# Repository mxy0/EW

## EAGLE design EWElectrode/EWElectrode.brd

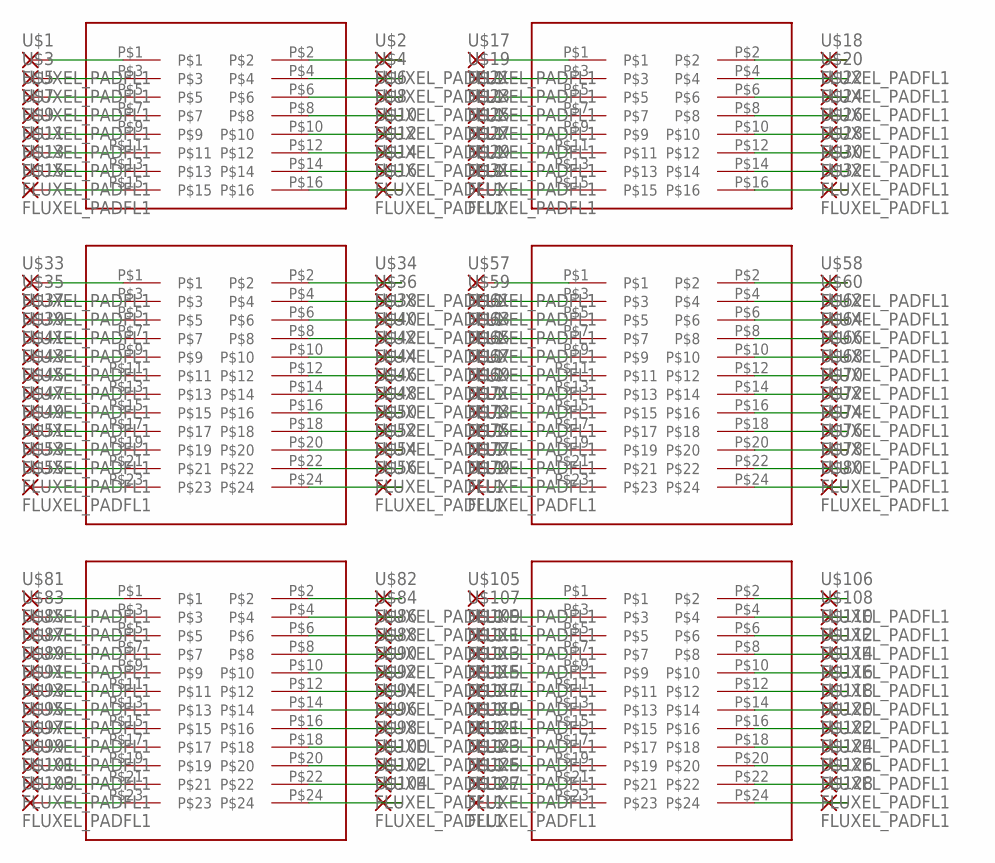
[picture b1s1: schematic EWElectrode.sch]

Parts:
J1, J2: M20-876P_8X2
J3, J4, J5, J6: M20-876P_12X2
U$1, U$2, U$3, U$4, U$5, U$6, U$7, U$8, U$9, U$10, U$11, U$12, U$13, U$14, U$15, U$16, U$17, U$18, U$19, U$20, U$21, U$22, U$23, U$24, U$25, U$26, U$27, U$28, U$29, U$30, U$31, U$32, U$33, U$34, U$35, U$36, U$37, U$38, U$39, U$40, U$41, U$42, U$43, U$44, U$45, U$46, U$47, U$48, U$49, U$50, U$51, U$52, U$53, U$54, U$55, U$56, U$57, U$58, U$59, U$60, U$61, U$62, U$63, U$64, U$65, U$66, U$67, U$68, U$69, U$70, U$71, U$72, U$73, U$74, U$75, U$76, U$77, U$78, U$79, U$80, U$81, U$82, U$83, U$84, U$85, U$86, U$87, U$88, U$89, U$90, U$91, U$92, U$93, U$94, U$95, U$96, U$97, U$98, U$99, U$100, U$101, U$102, U$103, U$104, U$105, U$106, U$107, U$108, U$109, U$110, U$111, U$112, U$113, U$114, U$115, U$116, U$117, U$118, U$119, U$120, U$121, U$122, U$123, U$124, U$125, U$126, U$127, U$128: FLUXEL_PADFL1; FLUXEL_PAD

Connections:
EW1: J1.P$1, U$1.1
EW2: J1.P$3, U$3.1
EW3: J1.P$5, U$5.1
EW4: J1.P$7, U$7.1
EW5: J1.P$9, U$9.1
EW6: J1.P$11, U$11.1
EW7: J1.P$13, U$13.1
EW8: J1.P$15, U$15.1
EW9: J1.P$2, U$2.1
EW10: J1.P$4, U$4.1
EW11: J1.P$6, U$6.1
EW12: J1.P$8, U$8.1
EW13: J1.P$10, U$10.1
EW14: J1.P$12, U$12.1
EW15: J1.P$14, U$14.1
EW16: J1.P$16, U$16.1
EW17: J2.P$1, U$17.1
EW18: J2.P$3, U$19.1
EW19: J2.P$5, U$21.1
EW20: J2.P$7, U$23.1
EW21: J2.P$9, U$25.1
EW22: J2.P$11, U$27.1
EW23: J2.P$13, U$29.1
EW24: J2.P$15, U$31.1
EW25: J2.P$2, U$18.1
EW26: J2.P$4, U$20.1
EW27: J2.P$6, U$22.1
EW28: J2.P$8, U$24.1
EW29: J2.P$10, U$26.1
EW30: J2.P$12, U$28.1
EW31: J2.P$14, U$30.1
EW32: J2.P$16, U$32.1
EW34: J3.P$3, U$35.1
EW35: J3.P$5, U$37.1
EW36: J3.P$7, U$39.1
EW37: J3.P$9, U$41.1
EW38: J3.P$11, U$43.1
EW39: J3.P$13, U$45.1
EW40: J3.P$15, U$47.1
EW41: J3.P$17, U$49.1
EW42: J3.P$19, U$51.1
EW44: J3.P$23, U$55.1
EW45: J3.P$2, U$34.1
EW46: J3.P$4, U$36.1
EW47: J3.P$6, U$38.1
EW48: J3.P$8, U$40.1
EW49: J3.P$10, U$42.1
EW50: J3.P$12, U$44.1
EW51: J3.P$14, U$46.1
EW52: J3.P$16, U$48.1
EW53: J3.P$18, U$50.1
EW54: J3.P$20, U$52.1
EW55: J3.P$22, U$54.1
EW56: J3.P$24, U$56.1
EW57: J4.P$1, U$57.1
EW58: J4.P$3, U$59.1
EW59: J4.P$5, U$61.1
EW60: J4.P$7, U$63.1
EW61: J4.P$9, U$65.1
EW62: J4.P$11, U$67.1
EW63: J4.P$13, U$69.1
EW64: J4.P$15, U$71.1
EW65: J4.P$17, U$73.1
EW66: J4.P$19, U$75.1
EW67: J4.P$21, U$77.1
EW68: J4.P$23, U$79.1
EW69: J4.P$2, U$58.1
EW70: J4.P$4, U$60.1
EW71: J4.P$6, U$62.1
EW72: J4.P$8, U$64.1
EW73: J4.P$10, U$66.1
EW74: J4.P$12, U$68.1
EW75: J4.P$14, U$70.1
EW76: J4.P$16, U$72.1
EW77: J4.P$18, U$74.1
EW78: J4.P$20, U$76.1
EW79: J4.P$22, U$78.1
EW80: J4.P$24, U$80.1
EW81: J5.P$1, U$81.1
EW82: J5.P$3, U$83.1
EW83: J5.P$5, U$85.1
EW84: J5.P$7, U$87.1
EW85: J5.P$9, U$89.1
EW86: J5.P$11, U$91.1
EW87: J5.P$13, U$93.1
EW88: J5.P$15, U$95.1
EW90: J5.P$19, U$99.1
EW91: J5.P$21, U$101.1
EW92: J5.P$23, U$103.1
EW93: J5.P$2, U$82.1
EW94: J5.P$4, U$84.1
EW95: J5.P$6, U$86.1
EW96: J5.P$8, U$88.1
EW97: J5.P$10, U$90.1
EW98: J5.P$12, U$92.1
EW99: J5.P$14, U$94.1
EW100: J5.P$16, U$96.1
EW102: J5.P$20, U$100.1
EW105: J6.P$1, U$105.1
EW106: J6.P$3, U$107.1
EW107: J6.P$5, U$109.1
EW108: J6.P$7, U$111.1
EW109: J6.P$9, U$113.1
EW110: J6.P$11, U$115.1
EW111: J6.P$13, U$117.1
EW112: J6.P$15, U$119.1
EW113: J6.P$17, U$121.1
EW114: J6.P$19, U$123.1
EW115: J6.P$21, U$125.1
EW116: J6.P$23, U$127.1
EW117: J6.P$2, U$106.1
EW118: J6.P$4, U$108.1
EW119: J6.P$6, U$110.1
EW120: J6.P$8, U$112.1
EW121: J6.P$10, U$114.1
EW122: J6.P$12, U$116.1
EW123: J6.P$14, U$118.1
EW124: J6.P$16, U$120.1
EW125: J6.P$18, U$122.1
EW126: J6.P$20, U$124.1
EW127: J6.P$22, U$126.1
EW128: J6.P$24, U$128.1
EW137: J3.P$21, U$53.1
EW166: J5.P$18, U$98.1
EW236: J5.P$17, U$97.1
EW261: J3.P$1, U$33.1
EW287: J5.P$22, U$102.1
EW289: J5.P$24, U$104.1

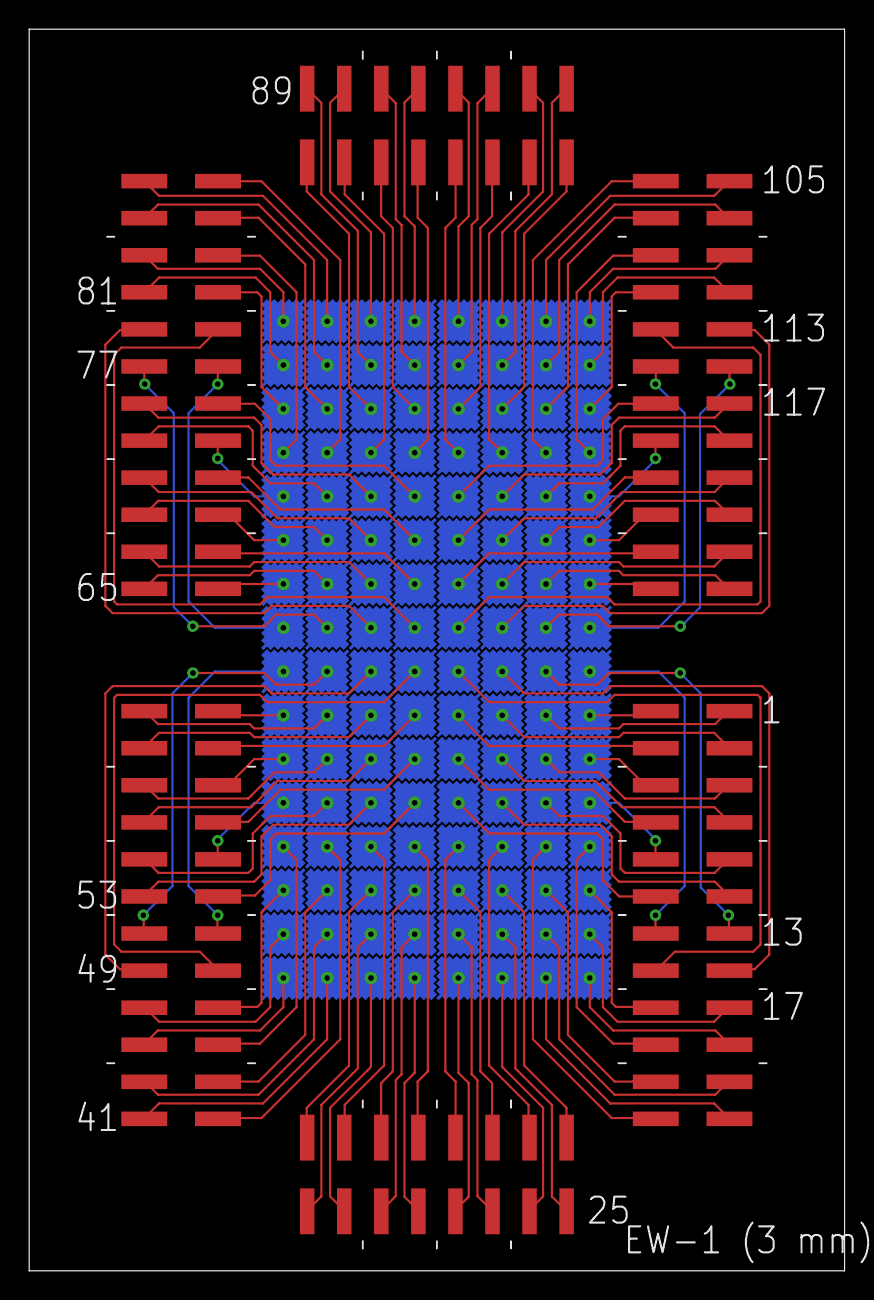
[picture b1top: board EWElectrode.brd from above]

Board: 2 copper layers, 55.9 x 85.1 mm, 134 parts (0 on the bottom side), 128 nets.

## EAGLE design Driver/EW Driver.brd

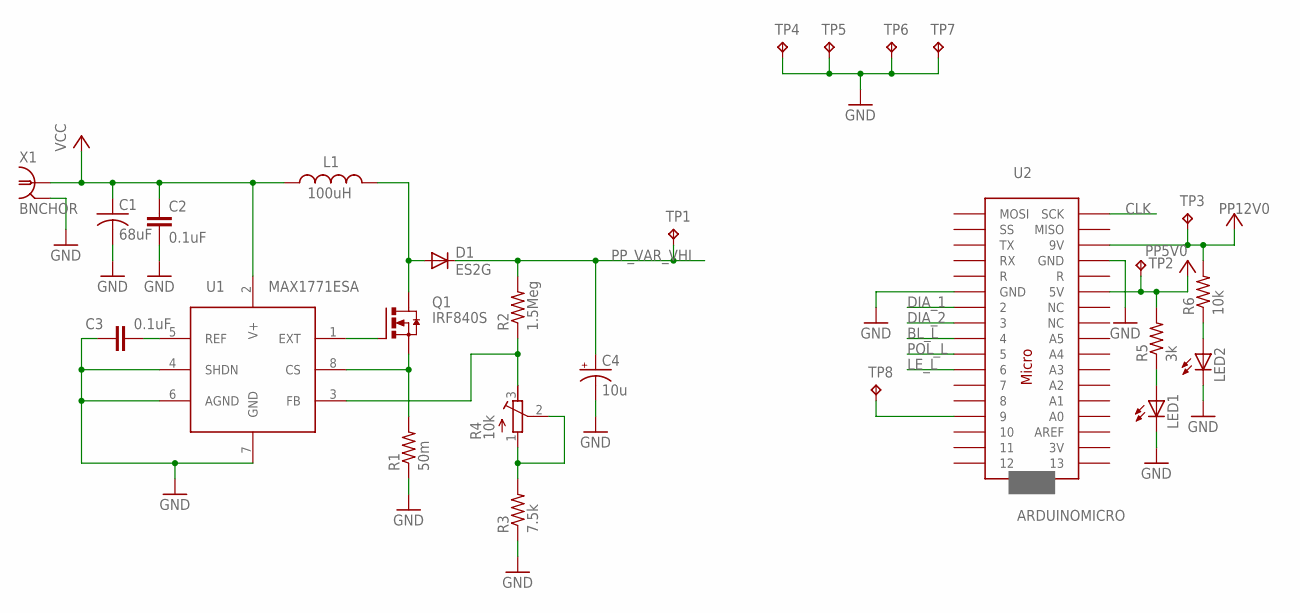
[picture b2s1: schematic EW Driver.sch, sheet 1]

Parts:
C1: 68uF; C2312
C2, C3: 0.1uF; C1206
C4: 10u; PANASONIC_D
D1: ES2G; DO214AA
L1: 100uH; P0762NL
LED1, LED2: LED_ESML0603; LED_SML0603
Q1: IRF840S; D2PACK
R1: 50m; R1206
R2: 1.5Meg; R1206
R3: 7.5k; R0805
R4: 10k; RTRIM3296P
R5: 3k; R0805
R6: 10k; R0805
TP1, TP2, TP3, TP8: TP; TEST_SMT
TP4, TP5, TP6, TP7: TP063; TEST_TH
U1: MAX1771ESA; SO08
U2: ARDUINOMICRO
X1: BNCHOR; BNC_HOR

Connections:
BL_L: U2.P$9 (4); also elsewhere on the board
CLK: U2.P$18 (SCK); also elsewhere on the board
DIA_1: U2.P$11 (2); also elsewhere on the board
DIA_2: U2.P$10 (3); also elsewhere on the board
GND: C1.2, C2.2, C3.2, C4.-, LED1.C, LED2.C, R1.1, R3.1, TP4.TP, TP5.TP, TP6.TP, TP7.TP, U1.4 (SHDN), U1.6 (AGND), U1.7 (GND), U2.P$12 (GND), U2.P$21 (GND), X1.2, X1.3 (2); also elsewhere on the board
LE_L: U2.P$7 (6); also elsewhere on the board
unnamed: C3.1, U1.5 (REF)
unnamed: Q1.1 (G), U1.1 (EXT)
unnamed: Q1.3 (S), R1.2, U1.8 (CS)
unnamed: D1.A, L1.2, Q1.2 (D)
unnamed: R3.2, R4.1 (A), R4.2 (S)
unnamed: R2.1, R4.3 (E), U1.3 (FB)
unnamed: LED1.A, R5.1
unnamed: LED2.A, R6.1
unnamed: TP8.TP, U2.P$4 (9)
POL_L: U2.P$8 (5); also elsewhere on the board
PP5V0: R5.2, TP2.TP, U2.P$23 (5V); also elsewhere on the board
PP12V0: C1.1, C2.1, L1.1, R6.2, TP3.TP, U1.2 (V+), U2.P$20 (9V), X1.1
PP_VAR_VHI: C4.+, D1.C, R2.2, TP1.TP; also elsewhere on the board

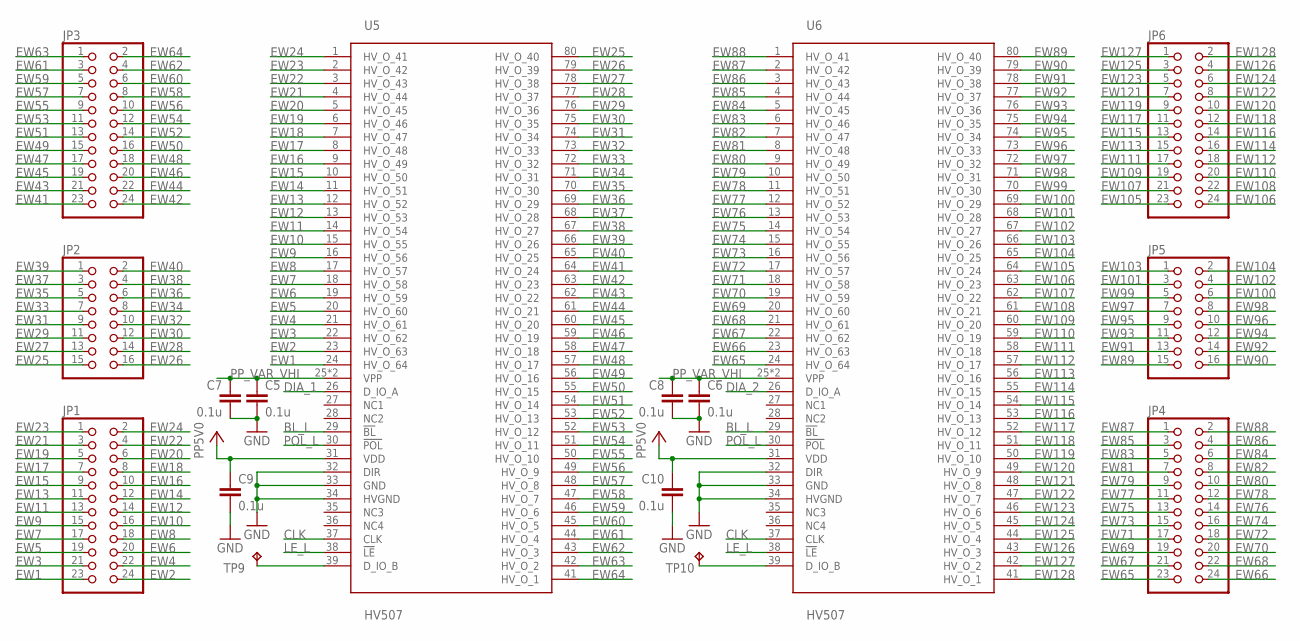
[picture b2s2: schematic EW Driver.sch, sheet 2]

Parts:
C5, C6, C7, C8, C9, C10: 0.1u; C1206
JP1, JP3, JP4, JP6: PINHD-2X12_0.05; 2X12_0.05
JP2, JP5: PINHD-2X8_0.05; 2X8_0.05
TP9, TP10: TP; TEST_SMT
U5, U6: HV507; HV507PG-G

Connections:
BL_L: U5.29 (!BL), U6.29 (!BL); also elsewhere on the board
CLK: U5.37 (CLK), U6.37 (CLK); also elsewhere on the board
DIA_1: U5.26 (D_IO_A); also elsewhere on the board
DIA_2: U6.26 (D_IO_A); also elsewhere on the board
EW1: JP1.23, U5.24 (HV_O_64)
EW2: JP1.24, U5.23 (HV_O_63)
EW3: JP1.21, U5.22 (HV_O_62)
EW4: JP1.22, U5.21 (HV_O_61)
EW5: JP1.19, U5.20 (HV_O_60)
EW6: JP1.20, U5.19 (HV_O_59)
EW7: JP1.17, U5.18 (HV_O_58)
EW8: JP1.18, U5.17 (HV_O_57)
EW9: JP1.15, U5.16 (HV_O_56)
EW10: JP1.16, U5.15 (HV_O_55)
EW11: JP1.13, U5.14 (HV_O_54)
EW12: JP1.14, U5.13 (HV_O_53)
EW13: JP1.11, U5.12 (HV_O_52)
EW14: JP1.12, U5.11 (HV_O_51)
EW15: JP1.9, U5.10 (HV_O_50)
EW16: JP1.10, U5.9 (HV_O_49)
EW17: JP1.7, U5.8 (HV_O_48)
EW18: JP1.8, U5.7 (HV_O_47)
EW19: JP1.5, U5.6 (HV_O_46)
EW20: JP1.6, U5.5 (HV_O_45)
EW21: JP1.3, U5.4 (HV_O_44)
EW22: JP1.4, U5.3 (HV_O_43)
EW23: JP1.1, U5.2 (HV_O_42)
EW24: JP1.2, U5.1 (HV_O_41)
EW25: JP2.15, U5.80 (HV_O_40)
EW26: JP2.16, U5.79 (HV_O_39)
EW27: JP2.13, U5.78 (HV_O_38)
EW28: JP2.14, U5.77 (HV_O_37)
EW29: JP2.11, U5.76 (HV_O_36)
EW30: JP2.12, U5.75 (HV_O_35)
EW31: JP2.9, U5.74 (HV_O_34)
EW32: JP2.10, U5.73 (HV_O_33)
EW33: JP2.7, U5.72 (HV_O_32)
EW34: JP2.8, U5.71 (HV_O_31)
EW35: JP2.5, U5.70 (HV_O_30)
EW36: JP2.6, U5.69 (HV_O_29)
EW37: JP2.3, U5.68 (HV_O_28)
EW38: JP2.4, U5.67 (HV_O_27)
EW39: JP2.1, U5.66 (HV_O_26)
EW40: JP2.2, U5.65 (HV_O_25)
EW41: JP3.23, U5.64 (HV_O_24)
EW42: JP3.24, U5.63 (HV_O_23)
EW43: JP3.21, U5.62 (HV_O_22)
EW44: JP3.22, U5.61 (HV_O_21)
EW45: JP3.19, U5.60 (HV_O_20)
EW46: JP3.20, U5.59 (HV_O_19)
EW47: JP3.17, U5.58 (HV_O_18)
EW48: JP3.18, U5.57 (HV_O_17)
EW49: JP3.15, U5.56 (HV_O_16)
EW50: JP3.16, U5.55 (HV_O_15)
EW51: JP3.13, U5.54 (HV_O_14)
EW52: JP3.14, U5.53 (HV_O_13)
EW53: JP3.11, U5.52 (HV_O_12)
EW54: JP3.12, U5.51 (HV_O_11)
EW55: JP3.9, U5.50 (HV_O_10)
EW56: JP3.10, U5.49 (HV_O_9)
EW57: JP3.7, U5.48 (HV_O_8)
EW58: JP3.8, U5.47 (HV_O_7)
EW59: JP3.5, U5.46 (HV_O_6)
EW60: JP3.6, U5.45 (HV_O_5)
EW61: JP3.3, U5.44 (HV_O_4)
EW62: JP3.4, U5.43 (HV_O_3)
EW63: JP3.1, U5.42 (HV_O_2)
EW64: JP3.2, U5.41 (HV_O_1)
EW65: JP4.23, U6.24 (HV_O_64)
EW66: JP4.24, U6.23 (HV_O_63)
EW67: JP4.21, U6.22 (HV_O_62)
EW68: JP4.22, U6.21 (HV_O_61)
EW69: JP4.19, U6.20 (HV_O_60)
EW70: JP4.20, U6.19 (HV_O_59)
EW71: JP4.17, U6.18 (HV_O_58)
EW72: JP4.18, U6.17 (HV_O_57)
EW73: JP4.15, U6.16 (HV_O_56)
EW74: JP4.16, U6.15 (HV_O_55)
EW75: JP4.13, U6.14 (HV_O_54)
EW76: JP4.14, U6.13 (HV_O_53)
EW77: JP4.11, U6.12 (HV_O_52)
EW78: JP4.12, U6.11 (HV_O_51)
EW79: JP4.9, U6.10 (HV_O_50)
EW80: JP4.10, U6.9 (HV_O_49)
EW81: JP4.7, U6.8 (HV_O_48)
EW82: JP4.8, U6.7 (HV_O_47)
EW83: JP4.5, U6.6 (HV_O_46)
EW84: JP4.6, U6.5 (HV_O_45)
EW85: JP4.3, U6.4 (HV_O_44)
EW86: JP4.4, U6.3 (HV_O_43)
EW87: JP4.1, U6.2 (HV_O_42)
EW88: JP4.2, U6.1 (HV_O_41)
EW89: JP5.15, U6.80 (HV_O_40)
EW90: JP5.16, U6.79 (HV_O_39)
EW91: JP5.13, U6.78 (HV_O_38)
EW92: JP5.14, U6.77 (HV_O_37)
EW93: JP5.11, U6.76 (HV_O_36)
EW94: JP5.12, U6.75 (HV_O_35)
EW95: JP5.9, U6.74 (HV_O_34)
EW96: JP5.10, U6.73 (HV_O_33)
EW97: JP5.7, U6.72 (HV_O_32)
EW98: JP5.8, U6.71 (HV_O_31)
EW99: JP5.5, U6.70 (HV_O_30)
EW100: JP5.6, U6.69 (HV_O_29)
EW101: JP5.3, U6.68 (HV_O_28)
EW102: JP5.4, U6.67 (HV_O_27)
EW103: JP5.1, U6.66 (HV_O_26)
EW104: JP5.2, U6.65 (HV_O_25)
EW105: JP6.23, U6.64 (HV_O_24)
EW106: JP6.24, U6.63 (HV_O_23)
EW107: JP6.21, U6.62 (HV_O_22)
EW108: JP6.22, U6.61 (HV_O_21)
EW109: JP6.19, U6.60 (HV_O_20)
EW110: JP6.20, U6.59 (HV_O_19)
EW111: JP6.17, U6.58 (HV_O_18)
EW112: JP6.18, U6.57 (HV_O_17)
EW113: JP6.15, U6.56 (HV_O_16)
EW114: JP6.16, U6.55 (HV_O_15)
EW115: JP6.13, U6.54 (HV_O_14)
EW116: JP6.14, U6.53 (HV_O_13)
EW117: JP6.11, U6.52 (HV_O_12)
EW118: JP6.12, U6.51 (HV_O_11)
EW119: JP6.9, U6.50 (HV_O_10)
EW120: JP6.10, U6.49 (HV_O_9)
EW121: JP6.7, U6.48 (HV_O_8)
EW122: JP6.8, U6.47 (HV_O_7)
EW123: JP6.5, U6.46 (HV_O_6)
EW124: JP6.6, U6.45 (HV_O_5)
EW125: JP6.3, U6.44 (HV_O_4)
EW126: JP6.4, U6.43 (HV_O_3)
EW127: JP6.1, U6.42 (HV_O_2)
EW128: JP6.2, U6.41 (HV_O_1)
GND: C5.2, C6.2, C7.2, C8.2, C9.2, C10.2, U5.32 (DIR), U5.33 (GND), U5.34 (HVGND), U6.32 (DIR), U6.33 (GND), U6.34 (HVGND); also elsewhere on the board
LE_L: U5.38 (!LE), U6.38 (!LE); also elsewhere on the board
unnamed: TP9.TP, U5.39 (D_IO_B)
unnamed: TP10.TP, U6.39 (D_IO_B)
POL_L: U5.30 (!POL), U6.30 (!POL); also elsewhere on the board
PP5V0: C9.1, C10.1, U5.31 (VDD), U6.31 (VDD); also elsewhere on the board
PP_VAR_VHI: C5.1, C6.1, C7.1, C8.1, U5.25 (VPP), U5.40 (VPP), U6.25 (VPP), U6.40 (VPP); also elsewhere on the board

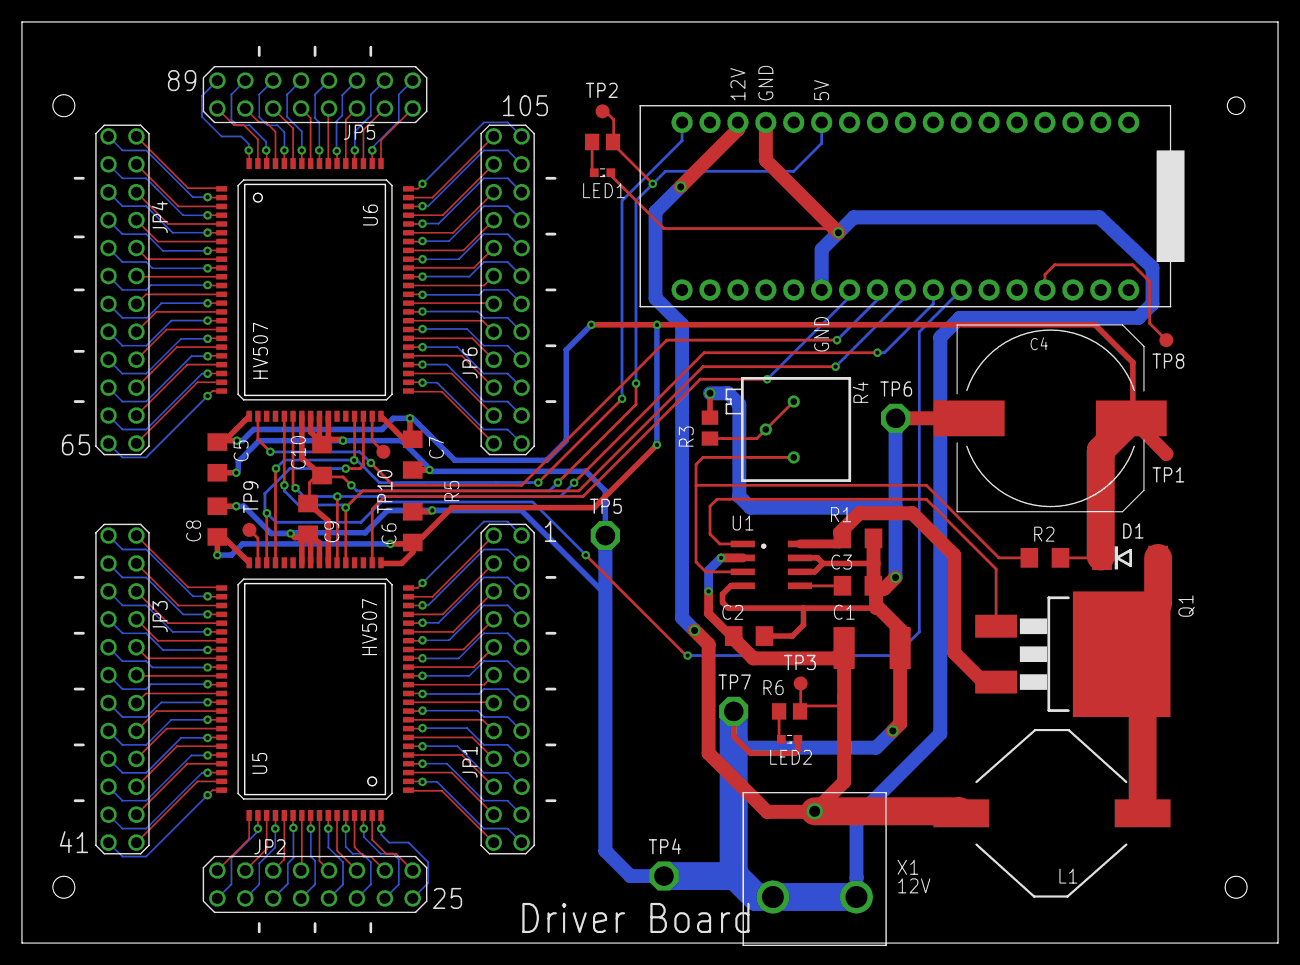
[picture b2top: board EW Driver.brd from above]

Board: 2 copper layers, 114.2 x 83.7 mm, 42 parts (0 on the bottom side), 149 nets.

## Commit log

2016-03-30 First commit of driver board. DRC and ERC pass. No board standoffs are included.
2016-04-04 Added standoff mounting holes and increased board size.
2016-05-09 Updated driver board ic orientation. EW board now interfaces with driver board. First iteration fo EW board with all electrodes connected. DRU updated for 6 mils traces. Ben.lbr updated with solderma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
2016-05-09 Updated driver board file location. EW board now interfaces with driver board (to be updated). First iteration fo EW board with all electrodes connected. Ben.lbr updated with soldermask stop for EW e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
2016-05-10 Removed old files.
2016-05-18 HV traces reduced to 6 mils. Silkscreen added for both boards.
